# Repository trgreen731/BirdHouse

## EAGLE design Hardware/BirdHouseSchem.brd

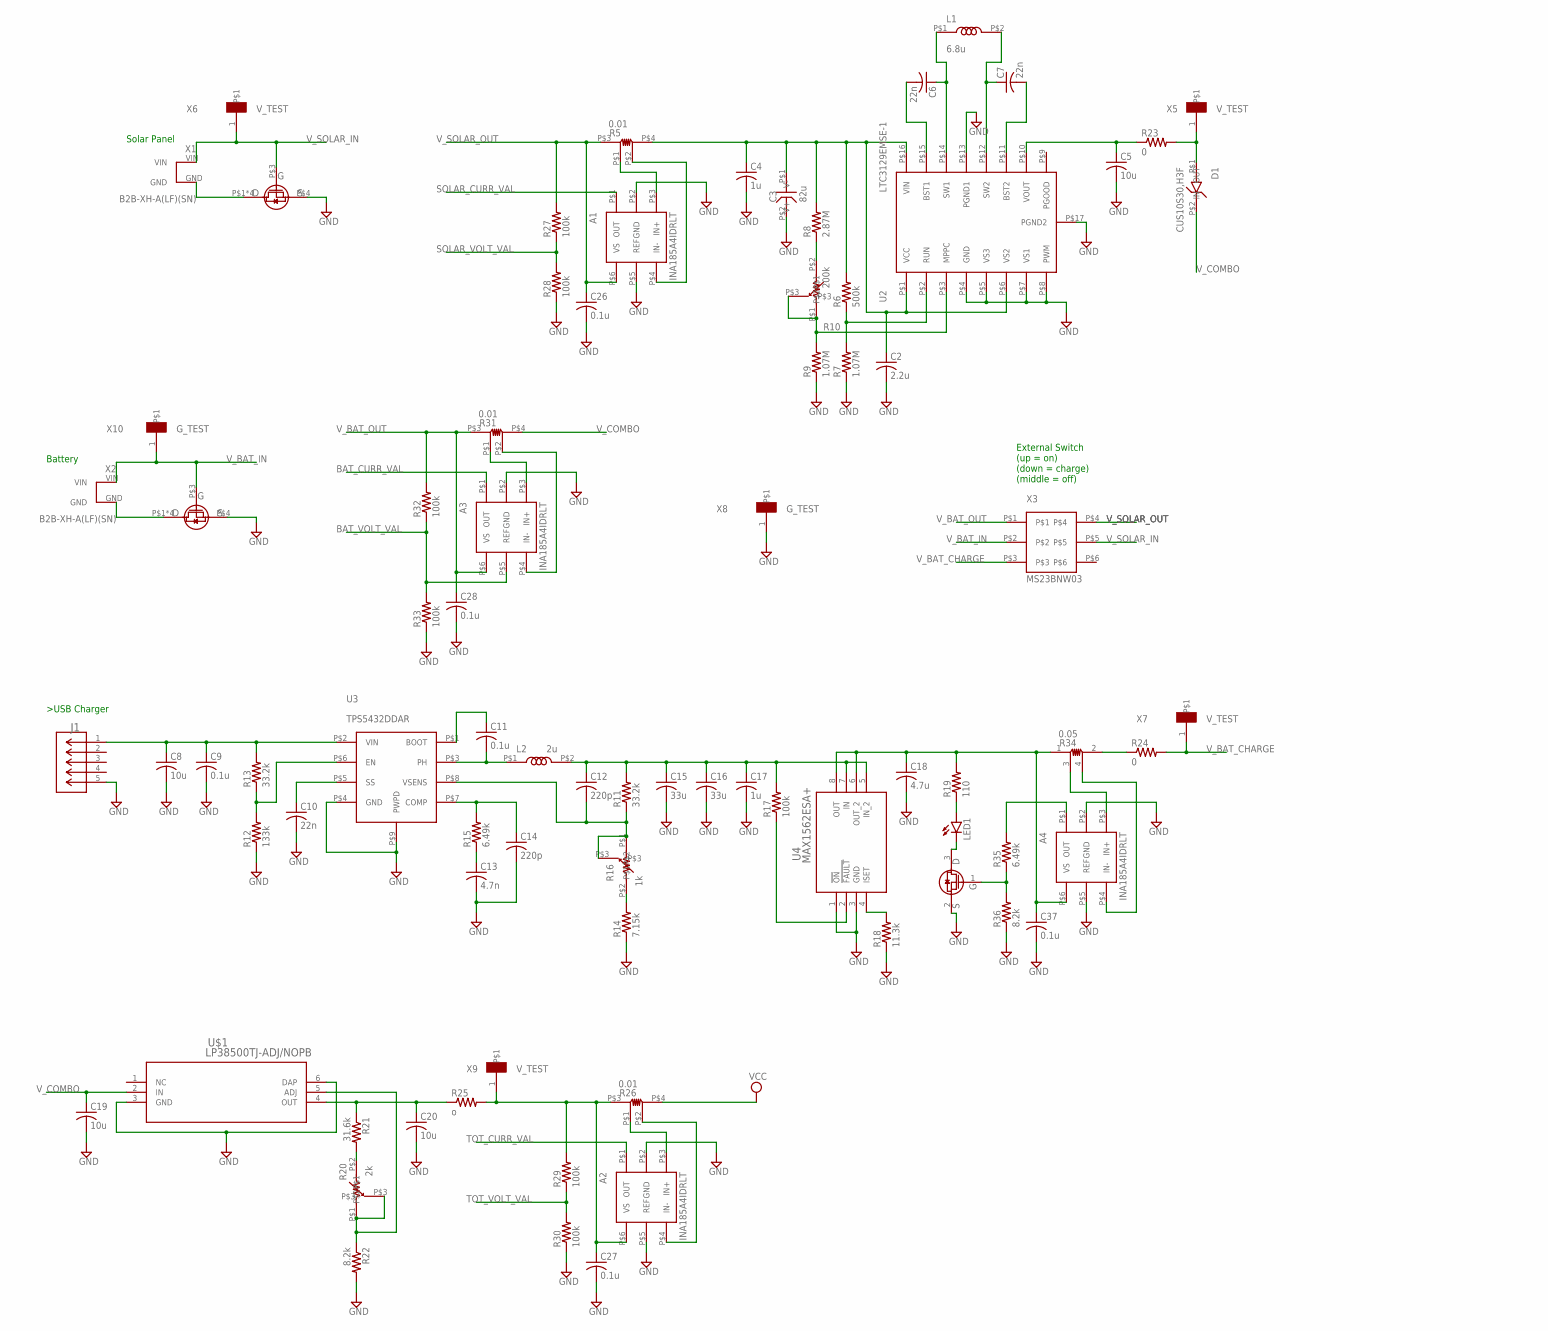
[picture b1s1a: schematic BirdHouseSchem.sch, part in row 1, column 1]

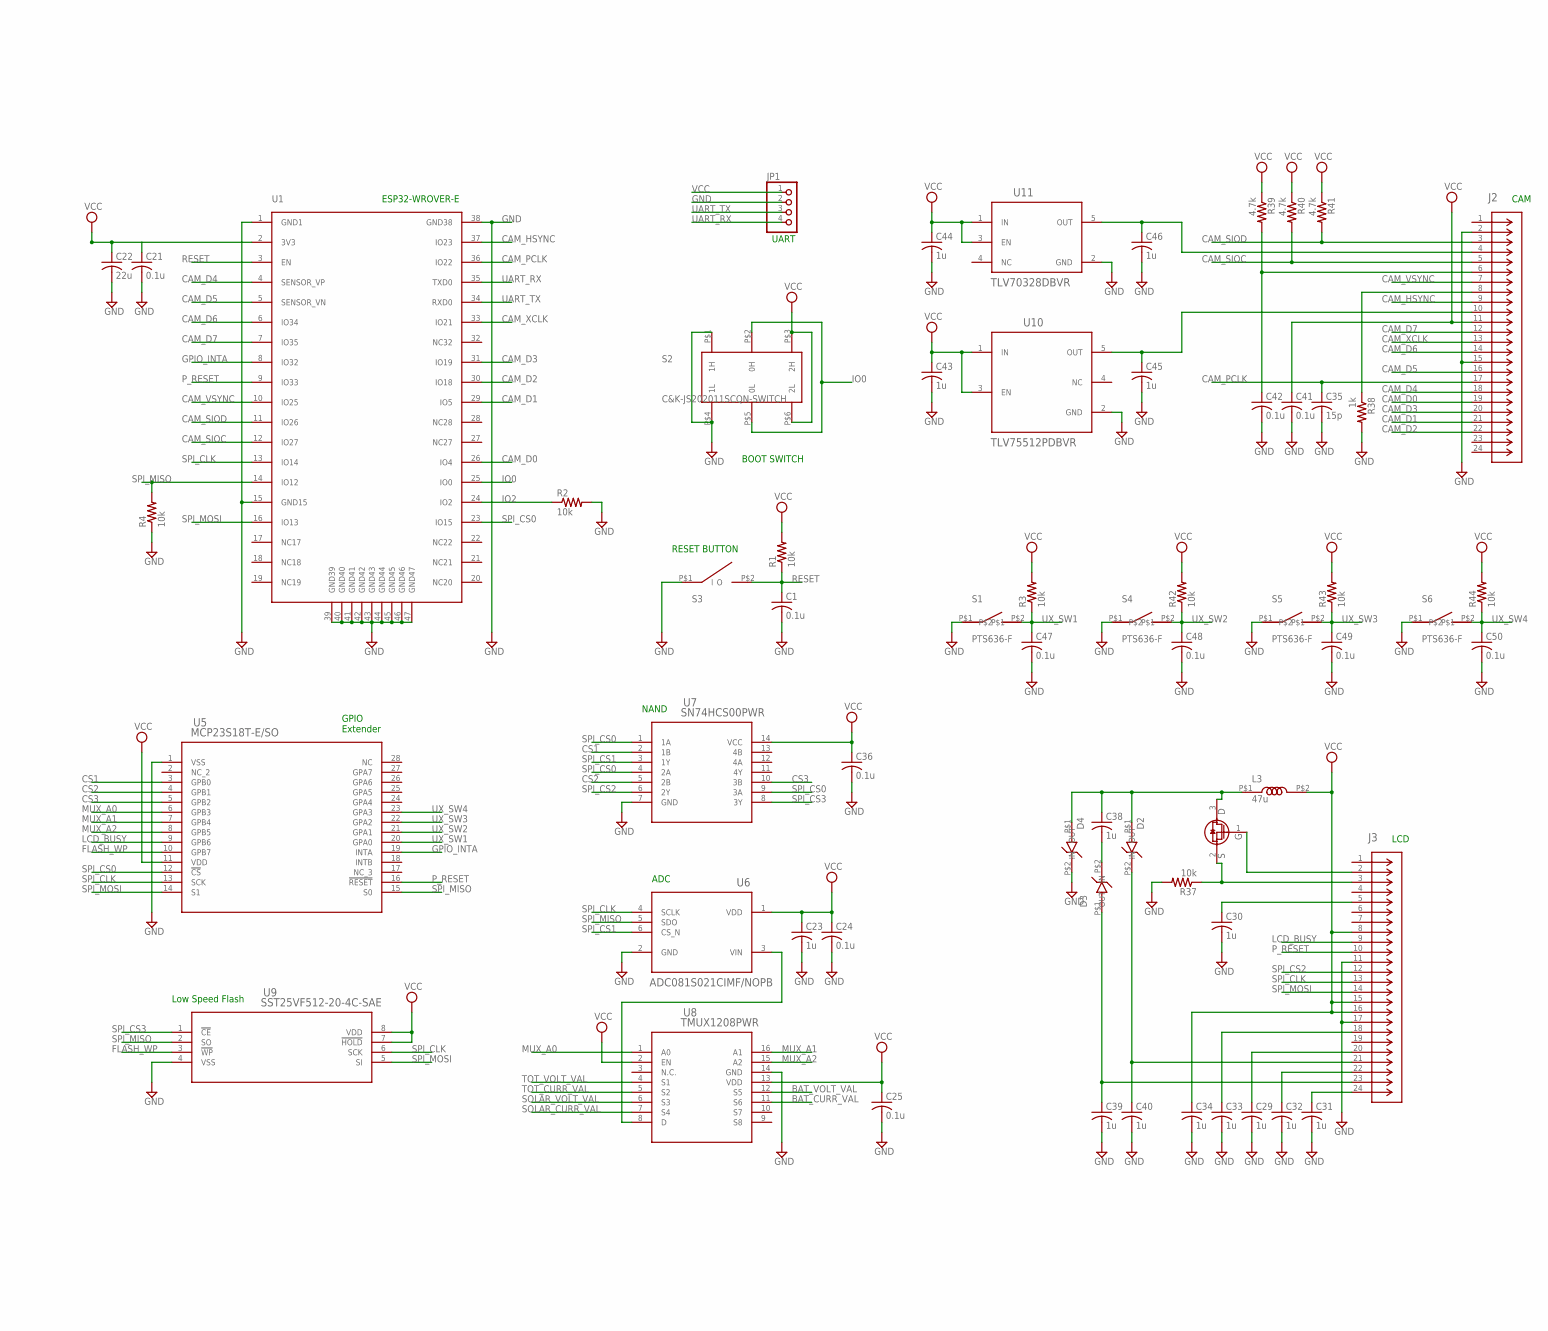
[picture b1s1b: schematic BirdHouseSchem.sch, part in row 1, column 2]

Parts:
A1, A2, A3, A4: INA185A4IDRLT; SOT-6
C1, C9, C11, C21, C24, C25, C26, C27, C28, C36, C37, C41, C42, C47, C48, C49, C50: 0.1u; C0805
C2: 2.2u; C0805
C3: 82u; EEE-FN1V820UP
C4, C17, C23, C29, C30, C31, C32, C33, C34, C38, C39, C40, C43, C44, C45, C46: 1u; C0805
C5, C8, C19, C20: 10u; C0805
C6, C7, C10: 22n; C0805
C12, C14: 220p; C0805
C13: 4.7n; C0805
C15, C16: 33u; C0805
C18: 4.7u; C0805
C22: 22u; C0805
C35: 15p; C0603
D1, D2, D3, D4: CUS10S30,H3F
J1: 10103594-0001LF; CONN_10103594-0001LF_AMP
J2, J3: FH40-24S-0.5SV; CONN_FH40-24S-0.5SV_HIR
JP1: PINHD-1X4; 1X04
L1: 6.8u; NRS8030T6R8MJGJ
L2: 2u; IHLP4040DZER2R0M11
L3: 47u; NRS8030T6R8MJGJ
LED1: LEDCHIP-LED0805; CHIP-LED0805
R1, R2, R3, R4, R37, R42, R43, R44: 10k; R0805
R5, R26, R31: 0.01; RL1632T4F-R005-FNH
R6: 500k; R0805
R7, R9: 1.07M; R0805
R8: 2.87M; R0805
R10: 200k; BOURNS-3361
R11, R13: 33.2k; R0603
R12: 133k; R0805
R14: 7.15k; R0805
R15, R35: 6.49k; R0805
R16: 1k; BOURNS-3361
R17, R27, R28, R29, R30, R32, R33: 100k; R0805
R18: 11.3k; R0805
R19: 110; R0805
R20: 2k; BOURNS-3361
R21: 31.6k; R0805
R22, R36: 8.2k; R0805
R23, R24: 0; R0805
R25: o; R0805
R34: 0.05; RL0816T4F-4
R38: 1k; R0805
R39, R40, R41: 4.7k; R0805
S1, S4, S5, S6: PTS636-F
S2: C&K-JS202011SCQN-SWITCH
S3: C&K-PTS636SL43SMTRLFS-PUSHBUTTON
TR1, TR2: SI3464DV-T1-BE3; TSOP-6
TR3: NX6008NBKW; SOT323
TR4: PMF250XNEX; SOT323
U1: ESP32-WROVER-E
U2: LTC3129EMSE-1
U3: TPS5432DDAR
U4: MAX1562ESA+; 21-0041_S8+2_MXM
U5: MCP23S18T-E/SO; SOIC28-W_MC_MCH
U6: ADC081S021CIMF/NOPB; DBV0006A_N
U7: SN74HCS00PWR; TSSOP14_PW_TEX
U8: TMUX1208PWR; PW_16_TEX
U9: SST25VF512-20-4C-SAE; SOIC8_SA_SST_MCH
U10: TLV75512PDBVR; DBV0005A_N
U11: TLV70328DBVR; DBV0005A-IPC_A
U$1: LP38500TJ-ADJ/NOPB; TJ5A
X1, X2: B2B-XH-A(LF)(SN)
X3: MS23BNW03
X5, X6, X7, X9: V_TEST
X8, X10: G_TEST; V_TEST

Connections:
BAT_CURR_VAL: A3.P$1 (OUT), U8.11 (S6)
BAT_VOLT_VAL: A3.P$5 (REF), R32.1, R33.2, U8.12 (S5)
CAM_D0: J2.19, U1.26 (IO4)
CAM_D1: J2.21, U1.29 (IO5)
CAM_D2: J2.22, U1.30 (IO18)
CAM_D3: J2.20, U1.31 (IO19)
CAM_D4: J2.18, U1.4 (SENSOR_VP)
CAM_D5: J2.16, U1.5 (SENSOR_VN)
CAM_D6: J2.14, U1.6 (IO34)
CAM_D7: J2.12, U1.7 (IO35)
CAM_HSYNC: J2.9, U1.37 (IO23)
CAM_PCLK: C35.1, J2.17, U1.36 (IO22)
CAM_SIOC: J2.5, R40.2, U1.12 (IO27)
CAM_SIOD: J2.3, R41.2, U1.11 (IO26)
CAM_VSYNC: J2.7, U1.10 (IO25)
CAM_XCLK: J2.13, U1.33 (IO21)
CS1: U5.3 (GPB0), U7.2 (1B)
CS2: U5.4 (GPB1), U7.5 (2B)
CS3: U5.5 (GPB2), U7.10 (3B)
FLASH_WP: U5.10 (GPB7), U9.3 (!WP)
GND: A1.P$2 (GND), A1.P$5 (REF), A2.P$2 (GND), A2.P$5 (REF), A3.P$2 (GND), A4.P$2 (GND), A4.P$5 (REF), C1.2, C2.2, C3.P$2 (V-), C4.2, C5.2, C8.2, C9.2, C10.2, C13.2, C14.2, C15.2, C16.2, C17.2, C18.2, C19.2, C20.2, C21.2, C22.2, C23.2, C24.2, C25.2, C26.2, C27.2, C28.2, C29.2, C30.2, C31.2, C32.2, C33.2, C34.2, C35.2, C36.2, C37.2, C39.2, C40.2, C41.2, C42.2, C43.2, C44.2, C45.2, C46.2, C47.2, C48.2, C49.2, C50.2, D4.P$2 (OUT), J1.5, J2.2, J2.15, J3.11, J3.17, JP1.2, R2.2, R4.1, R7.1, R9.1, R12.1, R14.1, R18.1, R22.2, R28.1, R30.1, R33.1, R36.1, R37.2, R38.2, S1.P$1, S2.P$1 (1H), S2.P$4 (1L), S3.P$1 (I), S4.P$1, S5.P$1, S6.P$1, TR1.P$4 (S), TR2.P$4 (S), TR3.2 (S), U1.1 (GND1), U1.15 (GND15), U1.38 (GND38), U1.39 (GND39), U1.40 (GND40), U1.41 (GND41), U1.42 (GND42), U1.43 (GND43), U1.44 (GND44), U1.45 (GND45), U1.46 (GND46), U1.47 (GND47), U2.P$4 (GND), U2.P$5 (VS3), U2.P$7 (VS1), U2.P$8 (PWM), U2.P$13 (PGND1), U2.P$17 (PGND2), U3.P$4 (GND), U3.P$9 (PWPD), U4.1 (!ON), U4.3 (GND), U5.1 (VSS), U6.2 (GND), U7.7 (GND), U8.14 (GND), U9.4 (VSS), U10.2 (GND), U11.2 (GND), U$1.3 (GND), U$1.6 (DAP), X8.1
GPIO_INTA: U1.8 (IO32), U5.19 (INTA)
IO0: S2.P$2 (0H), S2.P$5 (0L), U1.25 (IO0)
IO2: R2.1, U1.24 (IO2)
LCD_BUSY: J3.9, U5.9 (GPB6)
MUX_A0: U5.6 (GPB3), U8.1 (A0)
MUX_A1: U5.7 (GPB4), U8.16 (A1)
MUX_A2: U5.8 (GPB5), U8.15 (A2)
unnamed: A3.P$4 (IN-), R31.P$2 (V2)
unnamed: TR1.P$1 (D), TR1.P$2 (D), TR1.P$5 (D), TR1.P$6 (D), X1.GND
unnamed: C2.1, C3.P$1 (V+), C4.1, R5.P$4 (I2), R6.2, R8.2, U2.P$1 (VCC), U2.P$6 (VS2), U2.P$16 (VIN)
unnamed: A1.P$3 (IN+), R5.P$1 (V1)
unnamed: A1.P$4 (IN-), R5.P$2 (V2)
unnamed: TR2.P$1 (D), TR2.P$2 (D), TR2.P$5 (D), TR2.P$6 (D), X2.GND
unnamed: R6.1, R7.2, U2.P$2 (RUN)
unnamed: R9.2, R10.P$1, R10.P$3, U2.P$3 (MPPC)
unnamed: C6.1, L1.P$1, U2.P$14 (SW1)
unnamed: C5.1, R23.1, U2.P$10 (VOUT)
unnamed: C6.2, U2.P$15 (BST1)
unnamed: C7.1, L1.P$2, U2.P$12 (SW2)
unnamed: C7.2, U2.P$11 (BST2)
unnamed: C8.1, C9.1, J1.1, R13.2, U3.P$2 (VIN)
unnamed: R8.1, R10.P$2
unnamed: R12.2, R13.1, U3.P$6 (EN)
unnamed: C10.1, U3.P$5 (SS)
unnamed: C12.2, R11.1, R16.P$1, R16.P$3, U3.P$8 (VSENS)
unnamed: C14.1, R15.2, U3.P$7 (COMP)
unnamed: C13.1, R15.1
unnamed: R14.2, R16.P$2
unnamed: C11.2, L2.P$1, U3.P$3 (PH)
unnamed: C11.1, U3.P$1 (BOOT)
unnamed: C12.1, C15.1, C16.1, C17.1, L2.P$2, R11.2, R17.2, U4.5 (IN_2), U4.7 (IN)
unnamed: LED1.A, R19.1
unnamed: R17.1, U4.2 (!FAULT)
unnamed: R18.2, U4.4 (ISET)
unnamed: R20.P$1, R20.P$3, R22.1, U$1.5 (ADJ)
unnamed: R20.P$2, R21.2
unnamed: C20.1, R21.1, R25.1, U$1.4 (OUT)
unnamed: D1.P$1 (IN), R23.2, X5.1
unnamed: A3.P$3 (IN+), R31.P$1 (V1)
unnamed: A2.P$3 (IN+), R26.P$1 (V1)
unnamed: A2.P$4 (IN-), R26.P$2 (V2)
unnamed: A2.P$6 (VS), C27.1, R25.2, R26.P$3 (I1), R29.2, X9.1
unnamed: U6.3 (VIN), U8.8 (D)
unnamed: C33.1, J3.18
unnamed: C30.1, J3.5
unnamed: C29.1, J3.20
unnamed: C31.1, J3.24
unnamed: C32.1, J3.22
unnamed: A4.P$3 (IN+), R34.3 (V1)
unnamed: A4.P$4 (IN-), R34.4 (V2)
unnamed: R24.1, R34.2 (I2)
unnamed: A4.P$1 (OUT), R35.2
unnamed: R35.1, R36.2, TR3.1 (G)
unnamed: LED1.C, TR3.3 (D)
unnamed: J3.2, TR4.1 (G)
unnamed: J3.3, R37.1, TR4.2 (S)
unnamed: J2.8, R38.1
unnamed: C40.1, D2.P$2 (OUT), J3.21
unnamed: C38.1, D2.P$1 (IN), D4.P$1 (IN), L3.P$1, TR4.3 (D)
unnamed: C38.2, D3.P$2 (OUT)
unnamed: C39.1, D3.P$1 (IN), J3.23
unnamed: C42.1, J2.6, R39.2
unnamed: C46.1, J2.4, U11.5 (OUT)
unnamed: C45.1, J2.10, U10.5 (OUT)
unnamed: A4.P$6 (VS), C18.1, C37.1, R19.2, R34.1 (I1), U4.6 (OUT_2), U4.8 (OUT)
P_RESET: J3.10, U1.9 (IO33), U5.16 (!RESET)
RESET: C1.1, R1.1, S3.P$2 (O), U1.3 (EN)
SOLAR_CURR_VAL: A1.P$1 (OUT), U8.7 (S4)
SOLAR_VOLT_VAL: R27.1, R28.2, U8.6 (S3)
SPI_CLK: J3.13, U1.13 (IO14), U5.13 (SCK), U6.4 (SCLK), U9.6 (SCK)
SPI_CS0: U1.23 (IO15), U5.12 (!CS), U7.1 (1A), U7.4 (2A), U7.9 (3A)
SPI_CS1: U6.6 (CS_N), U7.3 (1Y)
SPI_CS2: J3.12, U7.6 (2Y)
SPI_CS3: U7.8 (3Y), U9.1 (!CE)
SPI_MISO: R4.2, U1.14 (IO12), U5.15 (S0), U6.5 (SDO), U9.2 (SO)
SPI_MOSI: J3.14, U1.16 (IO13), U5.14 (S1), U9.5 (SI)
TOT_CURR_VAL: A2.P$1 (OUT), U8.5 (S2)
TOT_VOLT_VAL: R29.1, R30.2, U8.4 (S1)
UART_RX: JP1.4, U1.35 (TXD0)
UART_TX: JP1.3, U1.34 (RXD0)
UX_SW1: C47.1, R3.1, S1.P$2, U5.20 (GPA0)
UX_SW2: C48.1, R42.1, S4.P$2, U5.21 (GPA1)
UX_SW3: C49.1, R43.1, S5.P$2, U5.22 (GPA2)
UX_SW4: C50.1, R44.1, S6.P$2, U5.23 (GPA3)
VCC: C21.1, C22.1, C23.1, C24.1, C25.1, C34.1, C36.1, C41.1, C43.1, C44.1, J2.11, J3.8, J3.15, J3.16, JP1.1, L3.P$2, R1.2, R3.2, R26.P$4 (I2), R39.1, R40.1, R41.1, R42.2, R43.2, R44.2, S2.P$3 (2H), S2.P$6 (2L), U1.2 (3V3), U5.11 (VDD), U6.1 (VDD), U7.14 (VCC), U8.2 (EN), U8.13 (VDD), U9.7 (!HOLD), U9.8 (VDD), U10.1 (IN), U10.3 (EN), U11.1 (IN), U11.3 (EN)
V_BAT_CHARGE: R24.2, X3.P$3, X7.1
V_BAT_IN: TR2.P$3 (G), X2.VIN, X3.P$2, X10.1
V_BAT_OUT: A3.P$6 (VS), C28.1, R31.P$3 (I1), R32.2, X3.P$1
V_COMBO: C19.1, D1.P$2 (OUT), R31.P$4 (I2), U$1.2 (IN)
V_SOLAR_IN: TR1.P$3 (G), X1.VIN, X3.P$5, X6.1
V_SOLAR_OUT: A1.P$6 (VS), C26.1, R5.P$3 (I1), R27.2, X3.P$4

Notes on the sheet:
UART
RESET BUTTON
BOOT SWITCH
ESP32-WROVER-E
Solar Panel
Battery
External Switch (up = on) (down = charge) (middle = off)
GPIO Extender
NAND
ADC
CAM
LCD
Low Speed Flash

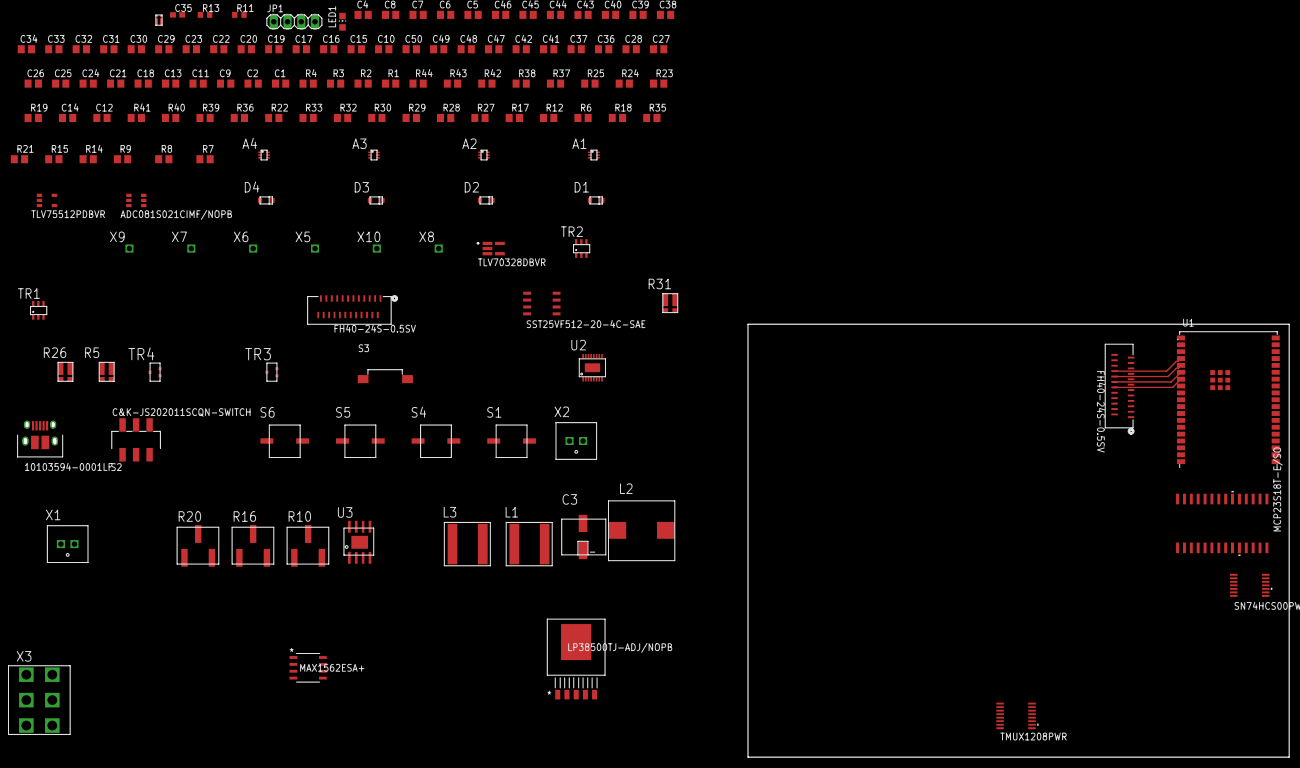
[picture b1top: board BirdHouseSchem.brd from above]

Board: 2 copper layers, 141 parts (0 on the bottom side), 112 nets.

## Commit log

2023-02-26 Hardware and References
2023-02-26 Software

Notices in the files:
parts and their libraries:
COPYRIGHT: Copyright (C) 2023 Ultra Librarian. All rights reserved.
